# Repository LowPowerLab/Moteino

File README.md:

Moteino
=======

Moteino Eagle project and library.
Moteino is now shipping with DualOptiboot: https://github.com/LowPowerLab/DualOptiboot
DualOptiboot allows for wireless programming using an external FLASH chip soldered to Moteino on the provided footprint.

#License
CC-BY-SA 4.0
https://creativecommons.org/licenses/by-sa/4.0/
You are free to share and adapt. But you need to give attribution and use the same license to redistribute.

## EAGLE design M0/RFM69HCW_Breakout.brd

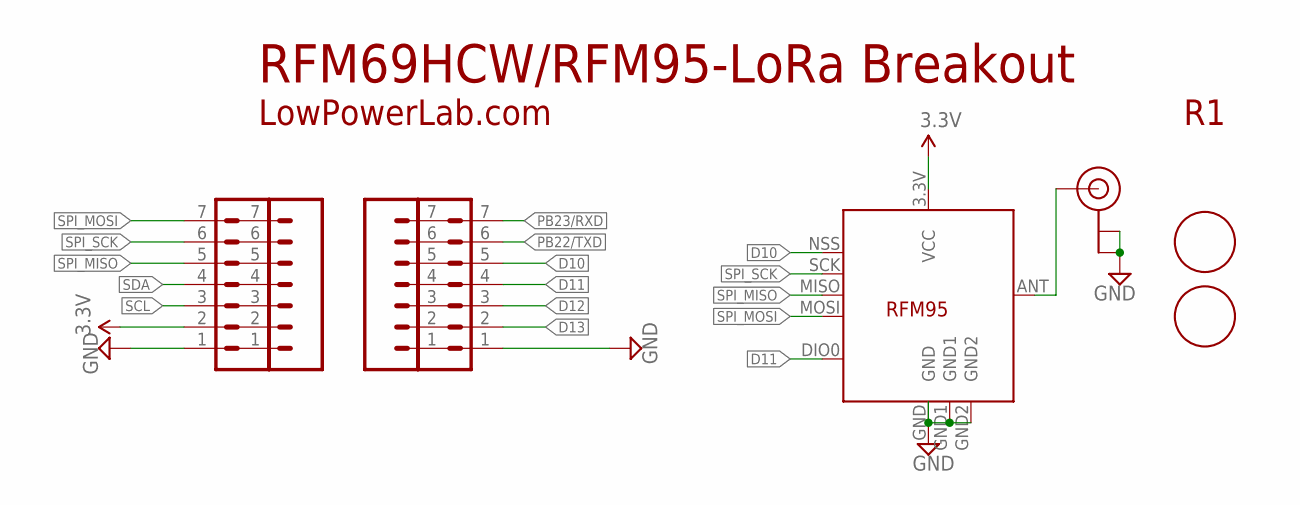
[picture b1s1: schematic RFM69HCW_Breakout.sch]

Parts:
FIDUCIAL_UPPERLEFT: FIDUCIAL1.5MM; FIDUCIAL_1.5MM
U$4, U$10: HDR_7PINNS_THINRINGS; 1X07_NS_THINRINGS
U$9: FIDUCIAL1.5MM; FIDUCIAL_1.5MM
U$16: RFM95COMPACT; RFM95
U$17, U$18: HDR_7PINHH; 1X07_NS_THINRINGS_HH
X2: U.FLW; U.FL_WIDER

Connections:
3.3V: U$16.3.3V (VCC), U$18.2
ANT: U$16.ANT, X2.SIGNAL
D10: U$16.NSS (SEL), U$17.5
D11: U$16.DIO0, U$17.4
D12: U$17.3
D13: U$17.2
GND: U$16.GND, U$16.GND1, U$16.GND2, U$17.1, U$18.1, X2.GND1 (GND), X2.GND2 (GND)
PB22/TXD: U$17.6
PB23/RXD: U$17.7
SCL: U$18.3
SDA: U$18.4
SPI_MISO: U$16.MISO, U$18.5
SPI_MOSI: U$16.MOSI, U$18.7
SPI_SCK: U$16.SCK, U$18.6

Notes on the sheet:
LowPowerLab.com
RFM69HCW/RFM95-LoRa Breakout

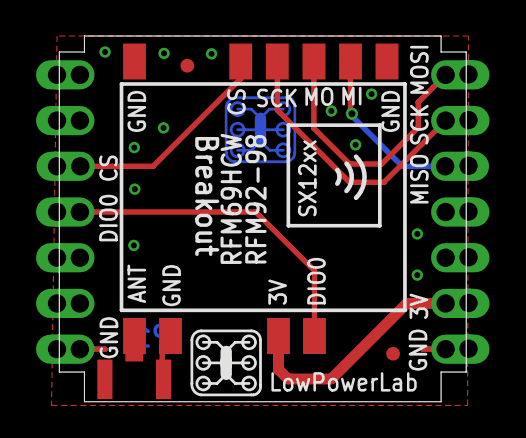
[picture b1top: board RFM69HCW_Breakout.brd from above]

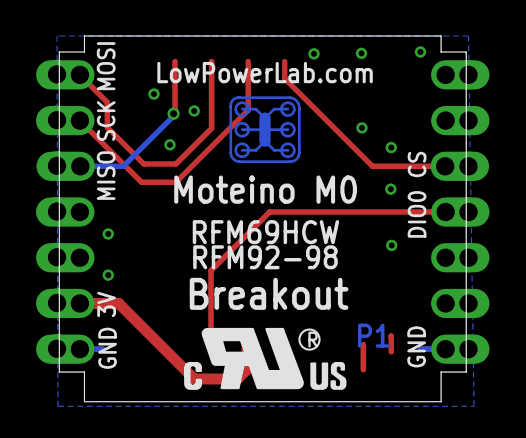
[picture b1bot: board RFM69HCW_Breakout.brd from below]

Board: 2 copper layers, 22.6 x 20.3 mm, 12 parts (4 on the bottom side), 8 nets.

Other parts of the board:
U$1: LOGO_LOWPOWERLAB
U$2: LOGO_UL
U$3: LOGO_LOWPOWERLAB_COPPER
U$7: LOGO_LOWPOWERLAB_STOP

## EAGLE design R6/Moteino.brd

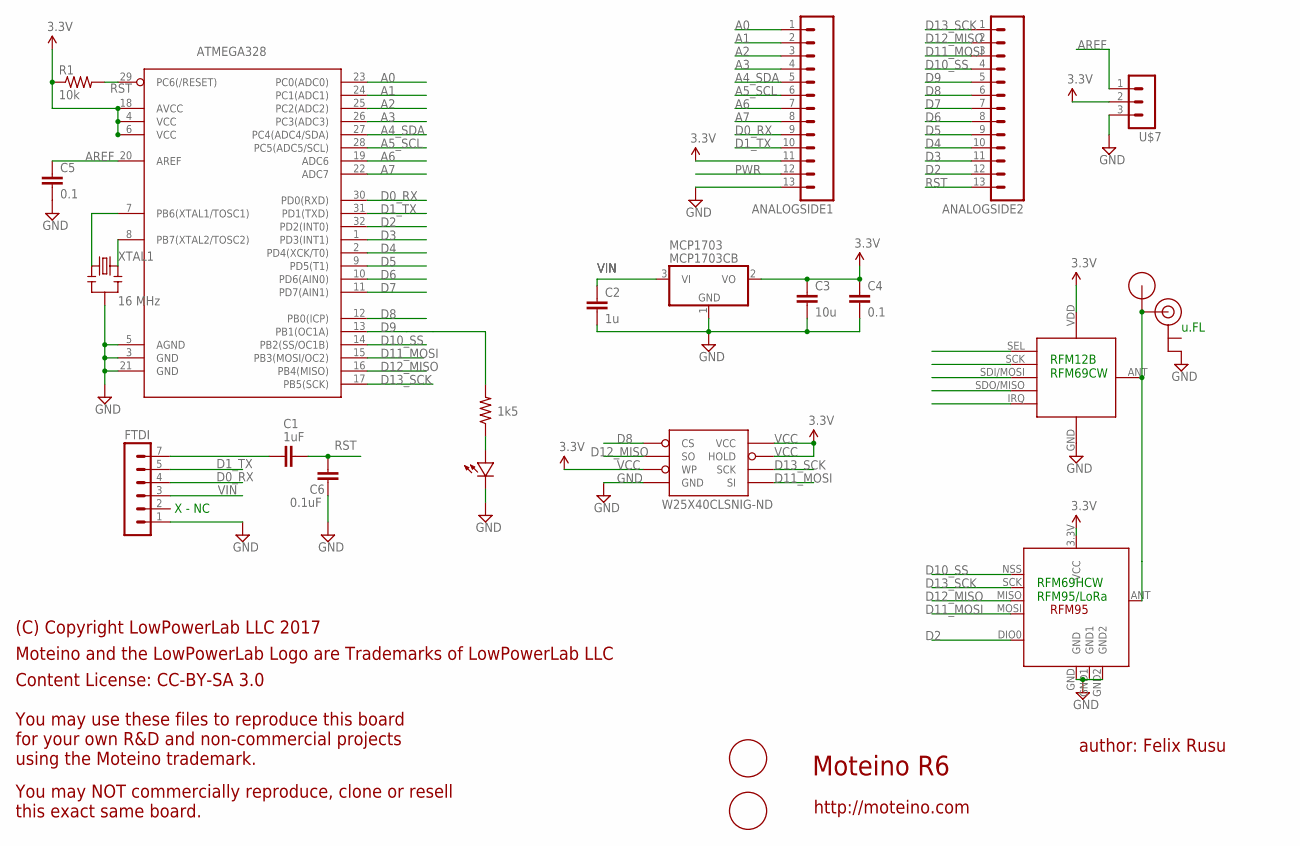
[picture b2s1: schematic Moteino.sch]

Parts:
ANALOGSIDE1, ANALOGSIDE2: HDR_13PINTHIN_RINGS; 1X13_THINRINGS
ATMEGA328: ATMega-328; TQFP32-08
C1: 1uF; 0603-CAP
C2: 1u; 0603-CAP
C3: 10u; 0805-CAP
C4, C5: 0.1; 0603-CAP
C6: 0.1uF; 0603-CAP
FTDI: HDR_6PINTHINRINGS; 1X06_NS_THINRINGS
LED: LED0603; 0603-LED
MCP1703: MCP1703CB; SOT23
R1: 10k; 0603-RES
R2: 1k5; 0603-RES
U$1: RFM12B_ANTENNA""; RFM12B-ANTENNA
U$2: RFM95LONGER; RFM95_LONGER
U$4: U.FL
U$5, U$6: FIDUCIAL1.5MM; FIDUCIAL_1.5MM
U$7: HDR_3PINTHINRINGS; 1X03_NS_THINRINGS
U$8: RFM12B_MINPADS; RFM12B-MINPADS
W25X40CLSNIG-ND: AT25F512BJEDEC_3.9MM; SO08
XTAL1: 16 MHz; RESONATOR-SMD

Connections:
A0: ANALOGSIDE1.1, ATMEGA328.23 (PC0(ADC0))
A1: ANALOGSIDE1.2, ATMEGA328.24 (PC1(ADC1))
A2: ANALOGSIDE1.3, ATMEGA328.25 (PC2(ADC2))
A3: ANALOGSIDE1.4, ATMEGA328.26 (PC3(ADC3))
A4_SDA: ANALOGSIDE1.5, ATMEGA328.27 (PC4(ADC4/SDA))
A5_SCL: ANALOGSIDE1.6, ATMEGA328.28 (PC5(ADC5/SCL))
A6: ANALOGSIDE1.7, ATMEGA328.19 (ADC6)
A7: ANALOGSIDE1.8, ATMEGA328.22 (ADC7)
AREF: ATMEGA328.20 (AREF), C5.1, U$7.1
D0_RX: ANALOGSIDE1.9, ATMEGA328.30 (PD0(RXD)), FTDI.4
D1_TX: ANALOGSIDE1.10, ATMEGA328.31 (PD1(TXD)), FTDI.5
D2: ANALOGSIDE2.12, ATMEGA328.32 (PD2(INT0)), U$2.DIO0, U$8.IRQ
D3: ANALOGSIDE2.11, ATMEGA328.1 (PD3(INT1))
D4: ANALOGSIDE2.10, ATMEGA328.2 (PD4(XCK/T0))
D5: ANALOGSIDE2.9, ATMEGA328.9 (PD5(T1))
D6: ANALOGSIDE2.8, ATMEGA328.10 (PD6(AIN0))
D7: ANALOGSIDE2.7, ATMEGA328.11 (PD7(AIN1))
D8: ANALOGSIDE2.6, ATMEGA328.12 (PB0(ICP)), W25X40CLSNIG-ND.1_CS (CS)
D9: ANALOGSIDE2.5, ATMEGA328.13 (PB1(OC1A)), R2.2
D10_SS: ANALOGSIDE2.4, ATMEGA328.14 (PB2(SS/OC1B)), U$2.NSS (SEL), U$8.SEL
D11_MOSI: ANALOGSIDE2.3, ATMEGA328.15 (PB3(MOSI/OC2)), U$2.MOSI, U$8.SDI/MOSI, W25X40CLSNIG-ND.5_SI (SI)
D12_MISO: ANALOGSIDE2.2, ATMEGA328.16 (PB4(MISO)), U$2.MISO, U$8.SDO/MISO, W25X40CLSNIG-ND.2_SO (SO)
D13_SCK: ANALOGSIDE2.1, ATMEGA328.17 (PB5(SCK)), U$2.SCK, U$8.SCK, W25X40CLSNIG-ND.6_SCK (SCK)
GND: ANALOGSIDE1.13, ATMEGA328.3 (GND), ATMEGA328.5 (AGND), ATMEGA328.21 (GND), C2.2, C3.2, C4.2, C5.2, C6.2, FTDI.1, LED.MINUS, MCP1703.1 (GND), U$2.GND, U$2.GND1, U$2.GND2, U$4.GND2 (GND), U$7.3, U$8.GND, W25X40CLSNIG-ND.4_GND (GND), XTAL1.2
unnamed: ATMEGA328.7 (PB6(XTAL1/TOSC1)), XTAL1.1
unnamed: LED.PLUS, R2.1
unnamed: U$1.P$1, U$2.ANT, U$4.SIGNAL, U$8.ANT
unnamed: C1.2, FTDI.7 (6)
unnamed: ATMEGA328.8 (PB7(XTAL2/TOSC2)), XTAL1.3
PWR: ANALOGSIDE1.12
RST: ANALOGSIDE2.13, ATMEGA328.29 (PC6(/RESET)), C1.1, C6.1, R1.2
VCC: ANALOGSIDE1.11, ATMEGA328.4 (VCC), ATMEGA328.6 (VCC), ATMEGA328.18 (AVCC), C3.1, C4.1, MCP1703.2 (VO), R1.1, U$2.3.3V (VCC), U$7.2, U$8.VDD, W25X40CLSNIG-ND.3_WP (WP), W25X40CLSNIG-ND.7_HOLD (HOLD), W25X40CLSNIG-ND.8_VCC (VCC)
VIN: C2.1, FTDI.3, MCP1703.3 (VI)

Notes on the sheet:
Moteino R6
author: Felix Rusu
http://moteino.com
RFM69HCW RFM95/LoRa
RFM12B RFM69CW
X - NC
u.FL
(C) Copyright LowPowerLab LLC 2017
Moteino and the LowPowerLab Logo are Trademarks of LowPowerLab LLC
Content License: CC-BY-SA 3.0
You may use these files to reproduce this board for your own R&D and non-commercial projects using the Moteino trademark.
You may NOT commercially reproduce, clone or resell this exact same board.

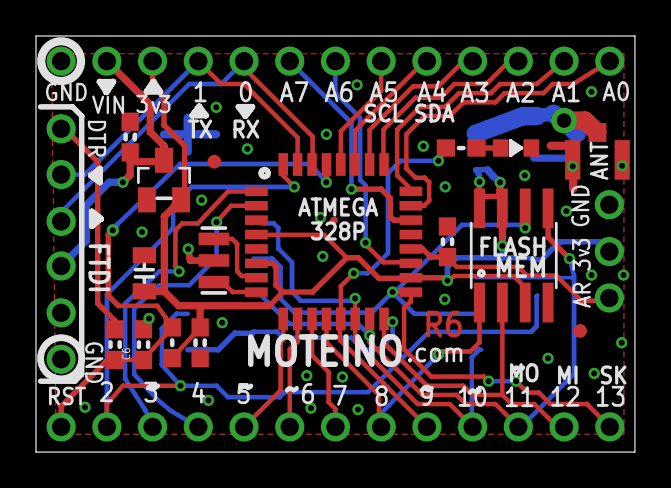
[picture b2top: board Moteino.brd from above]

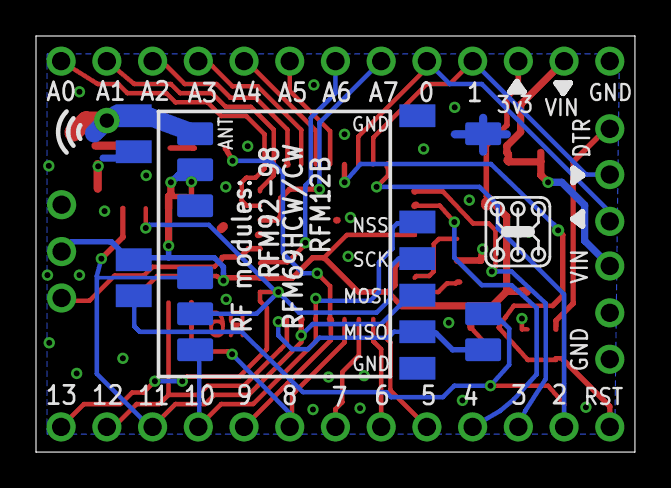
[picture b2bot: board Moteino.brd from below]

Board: 2 copper layers, 33.3 x 23.1 mm, 24 parts (3 on the bottom side), 32 nets.

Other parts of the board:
U$3: LOGO_LOWPOWERLAB

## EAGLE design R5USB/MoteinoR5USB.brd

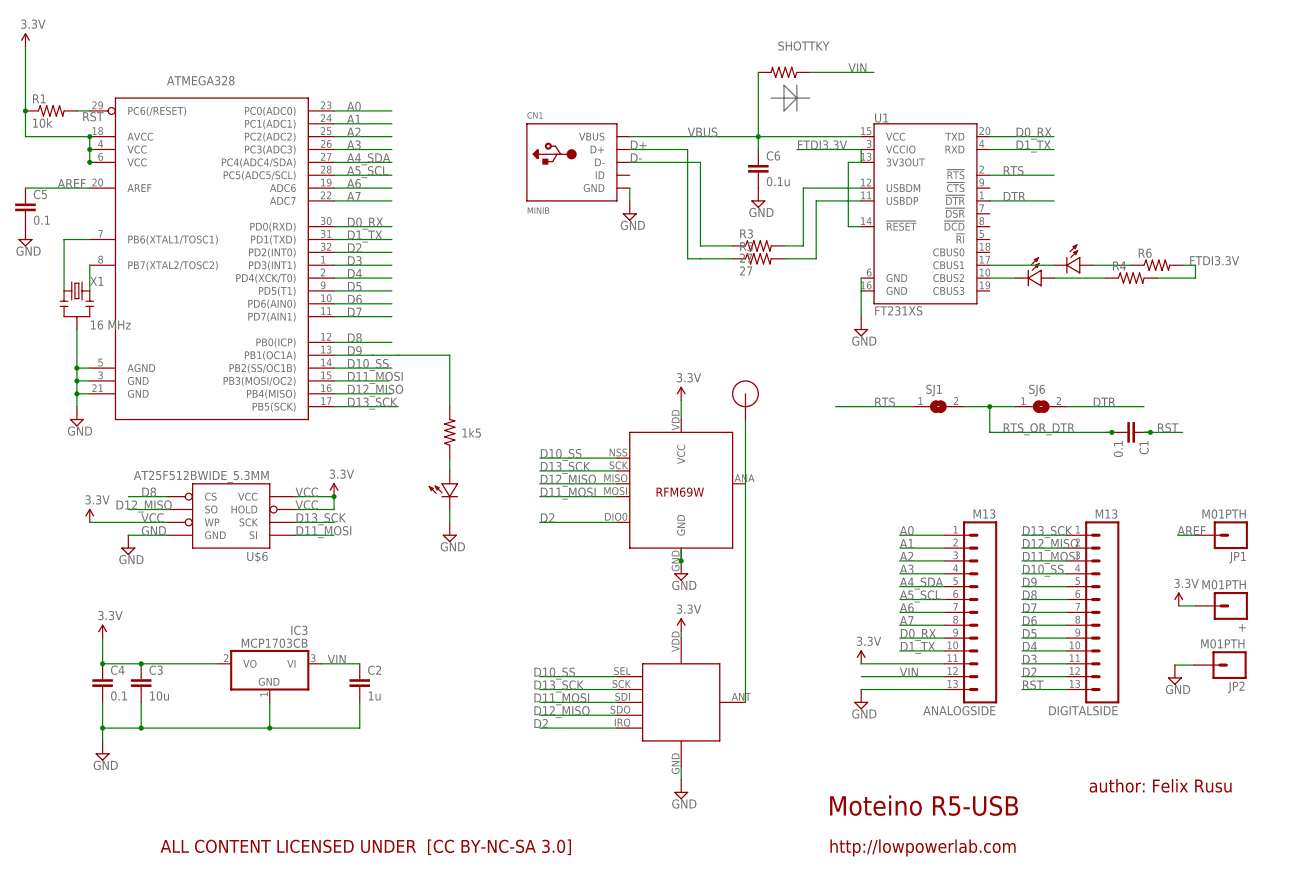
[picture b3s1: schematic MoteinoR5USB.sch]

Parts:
+: M01PTH; 1X01
ANALOGSIDE: M13; 1X13
ATMEGA328: ATMega-328; TQFP32-08
C1, C4, C5: 0.1; 0603-CAP
C2: 1u; 0603-CAP
C3: 10u; 0805-CAP
C6: 0.1u; 0603-CAP
CN1: MINIB; USB-MINIB
D: SHOTTKY; 0603-RES
DIGITALSIDE: M13; 1X13
IC3: MCP1703CB; SOT23
JP1, JP2: M01PTH; 1X01
R1: 10k; 0603-RES
R2: 1k5; 0603-RES
R3, R5: 27; 0603-RES
R4, R6: RESISTOR0603-RES; 0603-RES
RFM12B: RFM12B_MINPADS; RFM12B-MINPADS
SJ1, SJ6: JUMPER; SJW
U1: FT231XS; SSOP20_L
U$1: RFM12B_ANTENNA; RFM12B-ANTENNA
U$2, U$4, U$7: LED0603; 0603-LED
U$5: RFM69; RFM69W-MINPADS
U$6: AT25F512BWIDE_5.3MM; SO08WIDE
X1: 16 MHz; RESONATOR-SMD

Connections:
A0: ANALOGSIDE.1, ATMEGA328.23 (PC0(ADC0))
A1: ANALOGSIDE.2, ATMEGA328.24 (PC1(ADC1))
A2: ANALOGSIDE.3, ATMEGA328.25 (PC2(ADC2))
A3: ANALOGSIDE.4, ATMEGA328.26 (PC3(ADC3))
A4_SDA: ANALOGSIDE.5, ATMEGA328.27 (PC4(ADC4/SDA))
A5_SCL: ANALOGSIDE.6, ATMEGA328.28 (PC5(ADC5/SCL))
A6: ANALOGSIDE.7, ATMEGA328.19 (ADC6)
A7: ANALOGSIDE.8, ATMEGA328.22 (ADC7)
AREF: ATMEGA328.20 (AREF), C5.1, JP1.1
D0_RX: ANALOGSIDE.9, ATMEGA328.30 (PD0(RXD)), U1.20 (TXD)
D1_TX: ANALOGSIDE.10, ATMEGA328.31 (PD1(TXD)), U1.4 (RXD)
D2: ATMEGA328.32 (PD2(INT0)), DIGITALSIDE.12, RFM12B.IRQ, U$5.DIO0
D3: ATMEGA328.1 (PD3(INT1)), DIGITALSIDE.11
D4: ATMEGA328.2 (PD4(XCK/T0)), DIGITALSIDE.10
D5: ATMEGA328.9 (PD5(T1)), DIGITALSIDE.9
D6: ATMEGA328.10 (PD6(AIN0)), DIGITALSIDE.8
D7: ATMEGA328.11 (PD7(AIN1)), DIGITALSIDE.7
D8: ATMEGA328.12 (PB0(ICP)), DIGITALSIDE.6, U$6.1 (CS)
D9: ATMEGA328.13 (PB1(OC1A)), DIGITALSIDE.5, R2.2
D10_SS: ATMEGA328.14 (PB2(SS/OC1B)), DIGITALSIDE.4, RFM12B.SEL, U$5.NSS (SEL)
D11_MOSI: ATMEGA328.15 (PB3(MOSI/OC2)), DIGITALSIDE.3, RFM12B.SDI (SDI/MOSI), U$5.MOSI, U$6.5 (SI)
D12_MISO: ATMEGA328.16 (PB4(MISO)), DIGITALSIDE.2, RFM12B.SDO (SDO/MISO), U$5.MISO, U$6.2 (SO)
D13_SCK: ATMEGA328.17 (PB5(SCK)), DIGITALSIDE.1, RFM12B.SCK, U$5.SCK, U$6.6 (SCK)
D+: CN1.D+, R5.1
D-: CN1.D-, R3.1
DTR: SJ6.2, U1.1 (!DTR)
FTDI3.3V: R4.2, R6.2, U1.3 (VCCIO), U1.13 (3V3OUT), U1.14 (!RESET)
GND: ANALOGSIDE.13, ATMEGA328.3 (GND), ATMEGA328.5 (AGND), ATMEGA328.21 (GND), C2.2, C3.2, C4.2, C5.2, C6.2, CN1.GND, IC3.1 (GND), JP2.1, RFM12B.GND, U1.6 (GND), U1.16 (GND), U$2.MINUS, U$5.GND, U$6.4 (GND), X1.2
unnamed: ATMEGA328.7 (PB6(XTAL1/TOSC1)), X1.1
unnamed: R2.1, U$2.PLUS
unnamed: RFM12B.ANT, U$1.P$1, U$5.ANA (ANT)
unnamed: R3.2, U1.12 (USBDM)
unnamed: R5.2, U1.11 (USBDP)
unnamed: U1.17 (CBUS1), U$4.MINUS
unnamed: U1.10 (CBUS2), U$7.MINUS
unnamed: R4.1, U$7.PLUS
unnamed: R6.1, U$4.PLUS
unnamed: ATMEGA328.8 (PB7(XTAL2/TOSC2)), X1.3
RST: ATMEGA328.29 (PC6(/RESET)), C1.1, DIGITALSIDE.13, R1.2
RTS: SJ1.1, U1.2 (!RTS)
RTS_OR_DTR: C1.2, SJ1.2, SJ6.1
VBUS: C6.1, CN1.VBUS, D.2, U1.15 (VCC)
VCC: +.1, ANALOGSIDE.11, ATMEGA328.4 (VCC), ATMEGA328.6 (VCC), ATMEGA328.18 (AVCC), C3.1, C4.1, IC3.2 (VO), R1.1, RFM12B.VDD, U$5.VDD (VCC), U$6.3 (WP), U$6.7 (HOLD), U$6.8 (VCC)
VIN: ANALOGSIDE.12, C2.1, D.1, IC3.3 (VI)

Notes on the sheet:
Moteino R5-USB
author: Felix Rusu
http://lowpowerlab.com
ALL CONTENT LICENSED UNDER [CC BY-NC-SA 3.0]

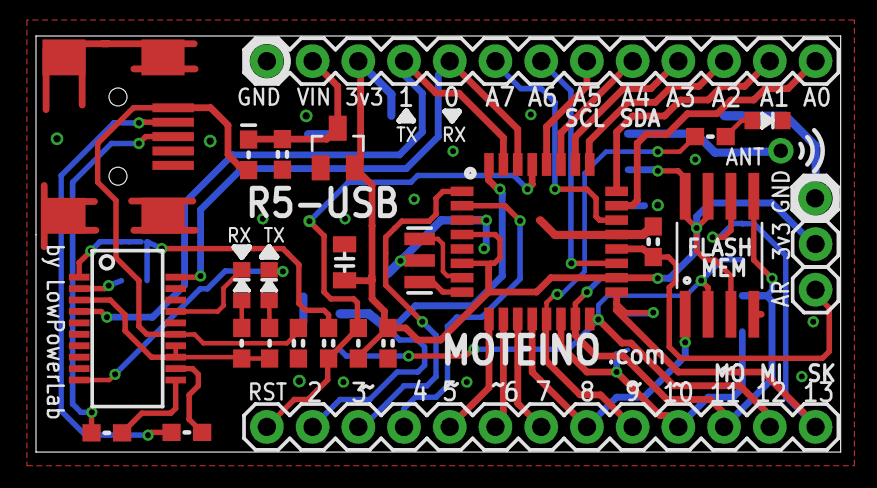
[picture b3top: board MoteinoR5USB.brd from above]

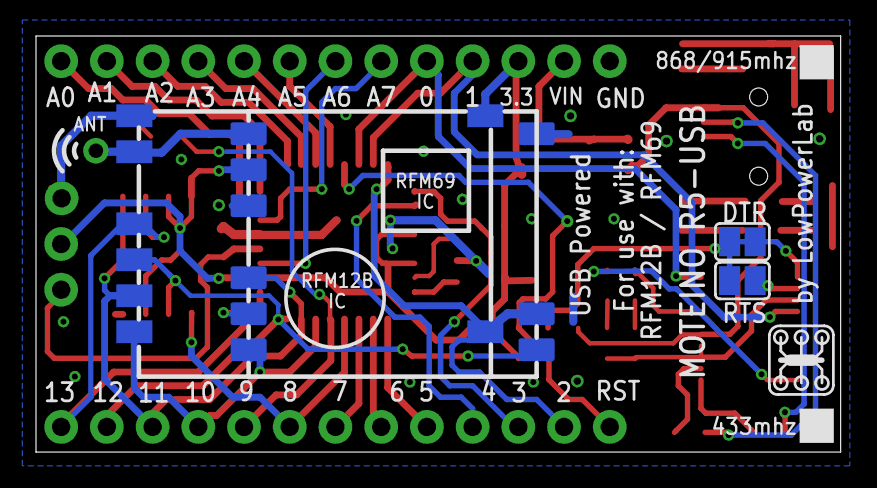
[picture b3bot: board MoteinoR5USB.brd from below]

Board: 2 copper layers, 44.7 x 23.1 mm, 33 parts (5 on the bottom side), 44 nets.

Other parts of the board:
U$3: LOGO_LOWPOWERLAB

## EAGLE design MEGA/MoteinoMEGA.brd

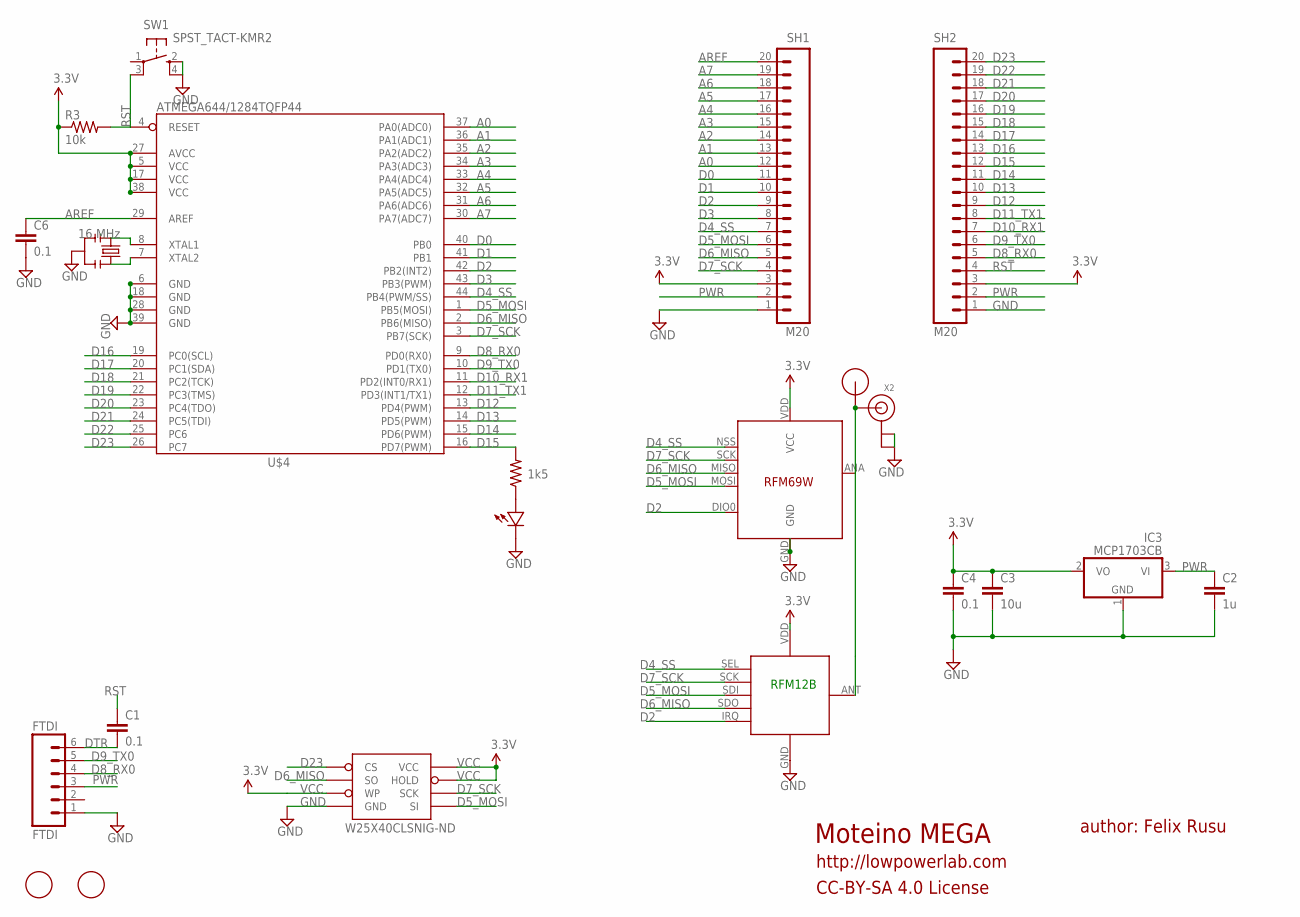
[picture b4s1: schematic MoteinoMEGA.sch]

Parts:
C1, C4, C6: 0.1; 0603-CAP
C2: 1u; 0603-CAP
C3: 10u; 0805-CAP
FTDI: FTDI; 1X06
IC3: MCP1703CB; SOT23
R2: 1k5; 0603-RES
R3: 10k; 0603-RES
RFM12B: RFM12B_MINPADS; RFM12B-MINPADS
SH1, SH2: M20; 1X20
SW1: SPST_TACT-KMR2; KMR2
U$1: RFM12B_ANTENNA; RFM12B-ANTENNA
U$2, U$7: FIDUCIAL; FIDUCIAL_1MM
U$4: ATMEGA644/1284TQFP44; TQFP44
U$5: RFM69; RFM69W-MINPADS
U$6: LED0603; 0603-LED
W25X40CLSNIG-ND: AT25F512BWIDE_5.3MM; SO08WIDE
X1: 16 MHz; RESONATOR-SMD
X2: ANTENNA_U.FL; U.FL

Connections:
A0: SH1.12, U$4.37 (PA0(ADC0))
A1: SH1.13, U$4.36 (PA1(ADC1))
A2: SH1.14, U$4.35 (PA2(ADC2))
A3: SH1.15, U$4.34 (PA3(ADC3))
A4: SH1.16, U$4.33 (PA4(ADC4))
A5: SH1.17, U$4.32 (PA5(ADC5))
A6: SH1.18, U$4.31 (PA6(ADC6))
A7: SH1.19, U$4.30 (PA7(ADC7))
AREF: C6.1, SH1.20, U$4.29 (AREF)
D0: SH1.11, U$4.40 (PB0)
D1: SH1.10, U$4.41 (PB1)
D2: RFM12B.IRQ, SH1.9, U$4.42 (PB2(INT2)), U$5.DIO0
D3: SH1.8, U$4.43 (PB3(PWM))
D4_SS: RFM12B.SEL, SH1.7, U$4.44 (PB4(PWM/SS)), U$5.NSS (SEL)
D5_MOSI: RFM12B.SDI (SDI/MOSI), SH1.6, U$4.1 (PB5(MOSI)), U$5.MOSI, W25X40CLSNIG-ND.5 (SI)
D6_MISO: RFM12B.SDO (SDO/MISO), SH1.5, U$4.2 (PB6(MISO)), U$5.MISO, W25X40CLSNIG-ND.2 (SO)
D7_SCK: RFM12B.SCK, SH1.4, U$4.3 (PB7(SCK)), U$5.SCK, W25X40CLSNIG-ND.6 (SCK)
D8_RX0: FTDI.4, SH2.5, U$4.9 (PD0(RX0))
D9_TX0: FTDI.5, SH2.6, U$4.10 (PD1(TX0))
D10_RX1: SH2.7, U$4.11 (PD2(INT0/RX1))
D11_TX1: SH2.8, U$4.12 (PD3(INT1/TX1))
D12: SH2.9, U$4.13 (PD4(PWM))
D13: SH2.10, U$4.14 (PD5(PWM))
D14: SH2.11, U$4.15 (PD6(PWM))
D15: R2.2, SH2.12, U$4.16 (PD7(PWM))
D16: SH2.13, U$4.19 (PC0(SCL))
D17: SH2.14, U$4.20 (PC1(SDA))
D18: SH2.15, U$4.21 (PC2(TCK))
D19: SH2.16, U$4.22 (PC3(TMS))
D20: SH2.17, U$4.23 (PC4(TDO))
D21: SH2.18, U$4.24 (PC5(TDI))
D22: SH2.19, U$4.25 (PC6)
D23: SH2.20, U$4.26 (PC7), W25X40CLSNIG-ND.1 (CS)
DTR: C1.2, FTDI.6
GND: C2.2, C3.2, C4.2, C6.2, FTDI.1, IC3.1 (GND), RFM12B.GND, SH1.1, SH2.1, SW1.2 (S), SW1.4 (S1), U$4.6 (GND), U$4.18 (GND), U$4.28 (GND), U$4.39 (GND), U$5.GND, U$6.MINUS, W25X40CLSNIG-ND.4 (GND), X1.2, X2.1 (GND), X2.2 (GND)
unnamed: U$4.8 (XTAL1), X1.1
unnamed: R2.1, U$6.PLUS
unnamed: RFM12B.ANT, U$1.P$1, U$5.ANA (ANT), X2.3 (SIGNAL)
unnamed: U$4.7 (XTAL2), X1.3
PWR: C2.1, FTDI.3, IC3.3 (VI), SH1.2, SH2.2
RST: C1.1, R3.2, SH2.4, SW1.3 (P1), U$4.4 (RESET)
VCC: C3.1, C4.1, IC3.2 (VO), R3.1, RFM12B.VDD, SH1.3, SH2.3, U$4.5 (VCC), U$4.17 (VCC), U$4.27 (AVCC), U$4.38 (VCC), U$5.VDD (VCC), W25X40CLSNIG-ND.3 (WP), W25X40CLSNIG-ND.7 (HOLD), W25X40CLSNIG-ND.8 (VCC)

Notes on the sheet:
Moteino MEGA
author: Felix Rusu
http://lowpowerlab.com
RFM12B
CC-BY-SA 4.0 License

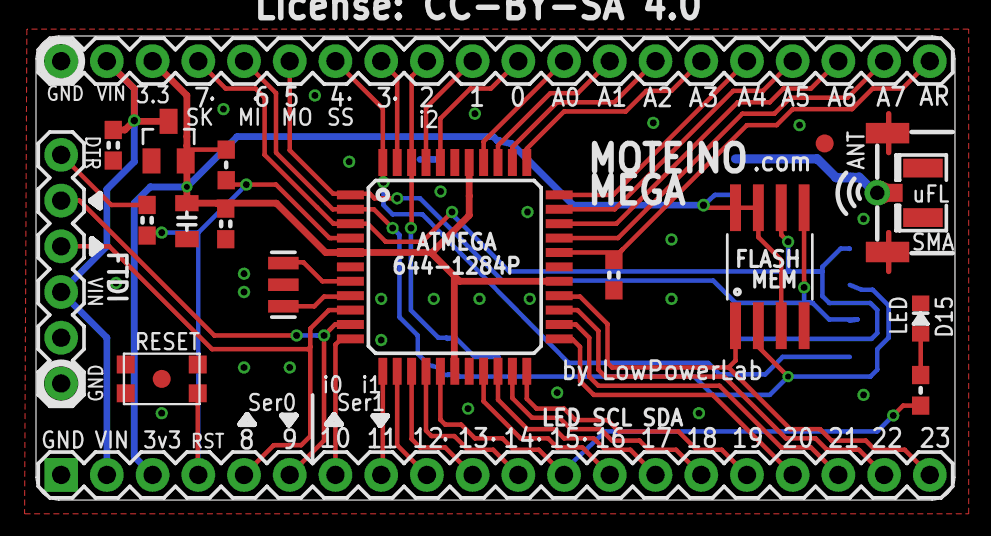
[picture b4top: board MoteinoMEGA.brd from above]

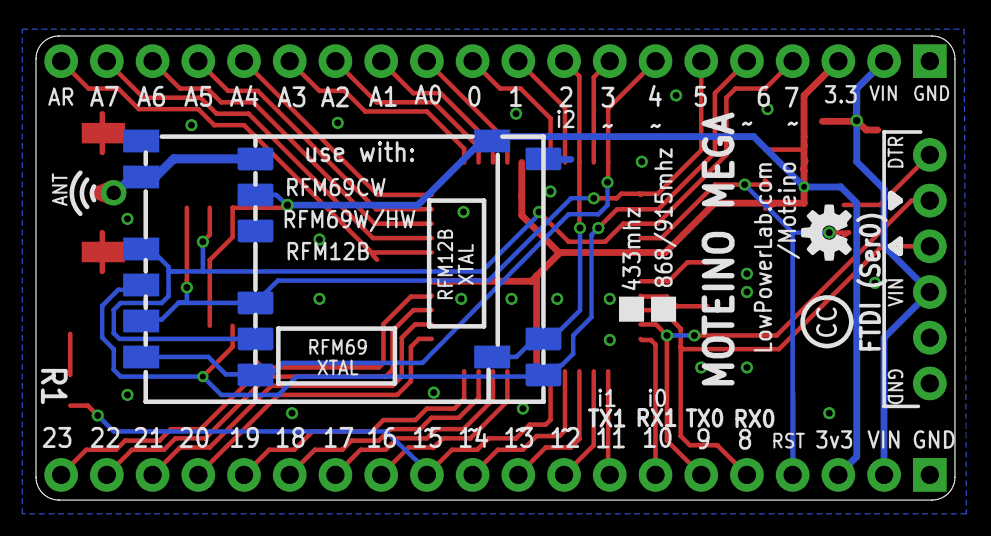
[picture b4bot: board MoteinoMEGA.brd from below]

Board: 2 copper layers, 51.1 x 25.8 mm, 23 parts (3 on the bottom side), 42 nets.

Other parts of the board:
U$3: OSHW-LOGO-S

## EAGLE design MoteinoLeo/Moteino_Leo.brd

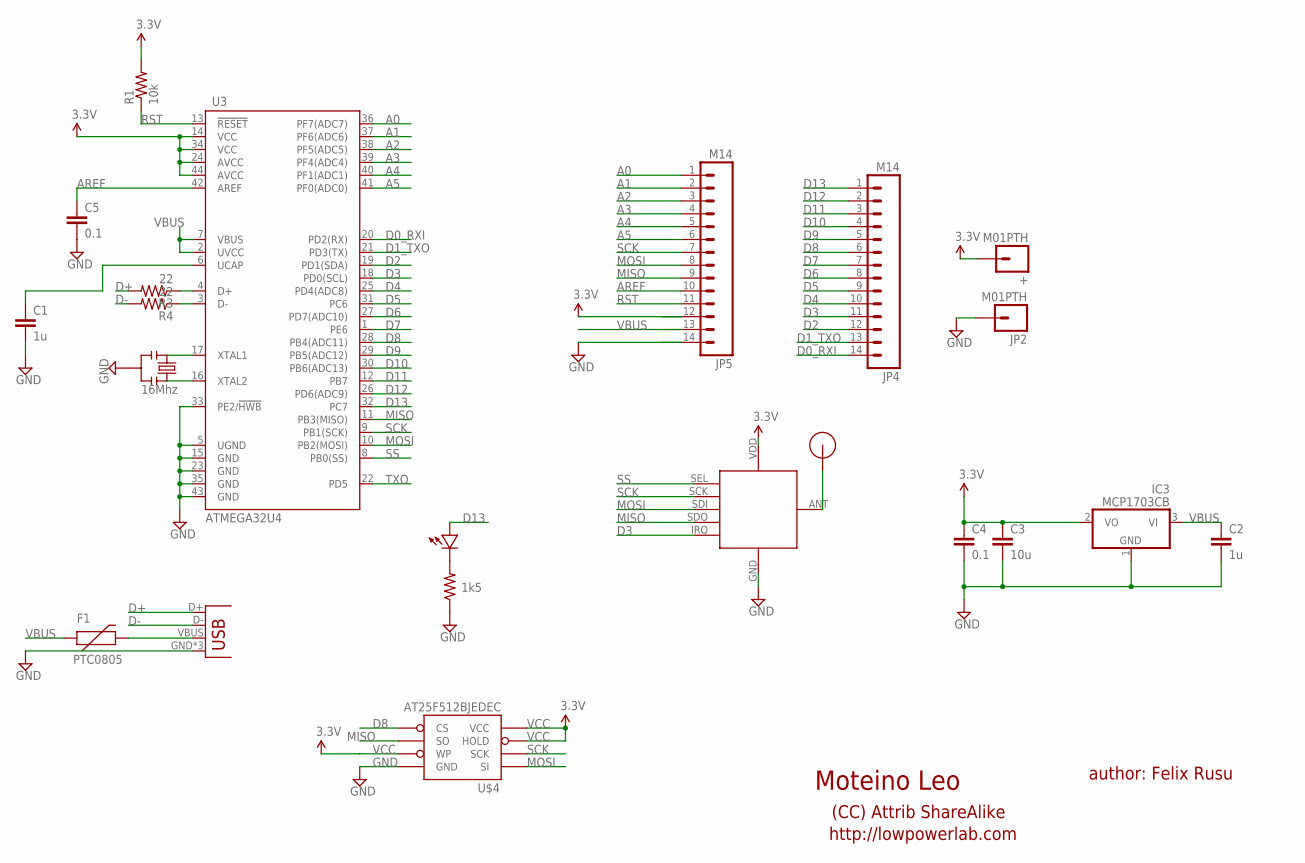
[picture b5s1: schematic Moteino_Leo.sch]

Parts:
+: M01PTH; 1X01
C1, C2: 1u; 0603-CAP
C3: 10u; 0805-CAP
C4, C5: 0.1; 0603-CAP
F1: PTC0805; 0805-PTC
IC3: MCP1703CB; SOT23
JP2: M01PTH; 1X01
JP3: USB-MICROB
JP4, JP5: M14; 1X14
R1: 10k; 0603-RES
R2: 1k5; 0603-RES
R3, R4: 22; 0603-RES
RFM12B: RFM12B_MINPADS; RFM12B-MINPADS
U3: ATMEGA32U4; QFN-44-NOPAD
U$1: RFM12B_ANTENNA; RFM12B-ANTENNA
U$2: LED0603; 0603-LED
U$4: AT25F512BJEDEC; SO08
X1: 16Mhz; RESONATOR-SMD

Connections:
A0: JP5.1, U3.36 (PF7(ADC7))
A1: JP5.2, U3.37 (PF6(ADC6))
A2: JP5.3, U3.38 (PF5(ADC5))
A3: JP5.4, U3.39 (PF4(ADC4))
A4: JP5.5, U3.40 (PF1(ADC1))
A5: JP5.6, U3.41 (PF0(ADC0))
AREF: C5.1, JP5.10, U3.42 (AREF)
D0_RXI: JP4.14, U3.20 (PD2(RX))
D1_TXO: JP4.13, U3.21 (PD3(TX))
D2: JP4.12, U3.19 (PD1(SDA))
D3: JP4.11, RFM12B.IRQ, U3.18 (PD0(SCL))
D4: JP4.10, U3.25 (PD4(ADC8))
D5: JP4.9, U3.31 (PC6)
D6: JP4.8, U3.27 (PD7(ADC10))
D7: JP4.7, U3.1 (PE6)
D8: JP4.6, U3.28 (PB4(ADC11)), U$4.1_CS (CS)
D9: JP4.5, U3.29 (PB5(ADC12))
D10: JP4.4, U3.30 (PB6(ADC13))
D11: JP4.3, U3.12 (PB7)
D12: JP4.2, U3.26 (PD6(ADC9))
D13: JP4.1, U3.32 (PC7), U$2.PLUS
D+: JP3.D+, R3.2
D-: JP3.D-, R4.2
GND: C1.2, C2.2, C3.2, C4.2, C5.2, IC3.1 (GND), JP2.1, JP3.GND, JP3.MT1 (GND), JP3.MT2 (GND), JP5.14, R2.1, RFM12B.GND, U3.5 (UGND), U3.15 (GND), U3.23 (GND), U3.33 (PE2/!HWB), U3.35 (GND), U3.43 (GND), U$4.4_GND (GND), X1.2
MISO: JP5.9, RFM12B.SDO (SDO/MISO), U3.11 (PB3(MISO)), U$4.2_SO (SO)
MOSI: JP5.8, RFM12B.SDI (SDI/MOSI), U3.10 (PB2(MOSI)), U$4.5_SI (SI)
unnamed: R2.2, U$2.MINUS
unnamed: RFM12B.ANT, U$1.P$1
unnamed: U3.16 (XTAL2), X1.3
unnamed: U3.17 (XTAL1), X1.1
unnamed: C1.1, U3.6 (UCAP)
unnamed: R3.1, U3.4 (D+)
unnamed: R4.1, U3.3 (D-)
RST: JP5.11, R1.1, U3.13 (!RESET)
SCK: JP5.7, RFM12B.SCK, U3.9 (PB1(SCK)), U$4.6_SCK (SCK)
SS: RFM12B.SEL, U3.8 (PB0(SS))
TXO: U3.22 (PD5)
USBPOWER: F1.2, JP3.VBUS
VBUS: C2.1, F1.1, IC3.3 (VI), JP5.13, U3.2 (UVCC), U3.7 (VBUS)
VCC: +.1, C3.1, C4.1, IC3.2 (VO), JP5.12, R1.2, RFM12B.VDD, U3.14 (VCC), U3.24 (AVCC), U3.34 (VCC), U3.44 (AVCC), U$4.3_WP (WP), U$4.7_HOLD (HOLD), U$4.8_VCC (VCC)

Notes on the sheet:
Moteino Leo
author: Felix Rusu
http://lowpowerlab.com
(CC) Attrib ShareAlike

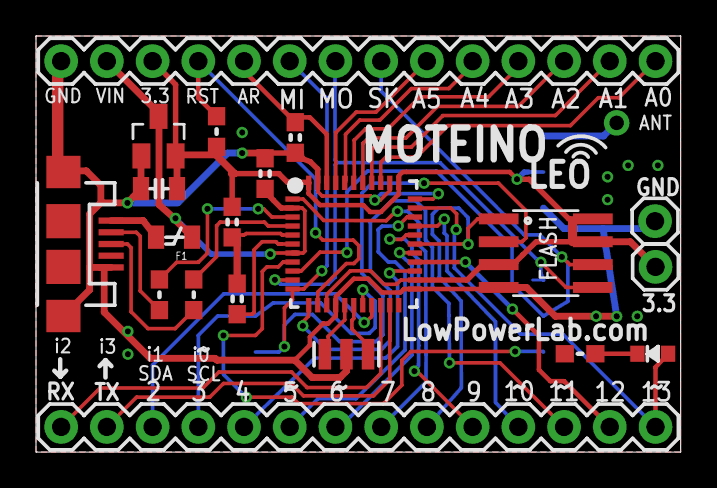
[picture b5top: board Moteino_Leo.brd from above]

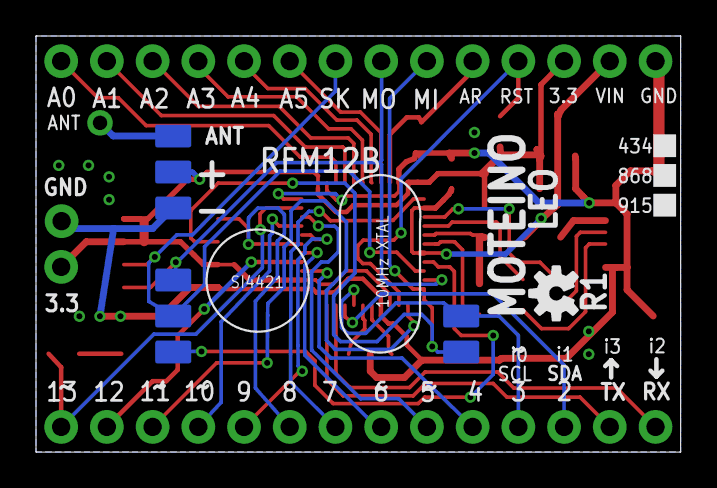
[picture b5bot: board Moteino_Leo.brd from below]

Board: 2 copper layers, 35.8 x 23.1 mm, 23 parts (2 on the bottom side), 39 nets.

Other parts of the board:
U$3: OSHW-LOGO-S

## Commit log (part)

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2012-12-28 Add Moteino Eagle files
2013-03-12 R2 Update
2013-05-30 Update to R1 production schematic
2013-05-30 Update to R1 production board
2013-06-25 Add R2 and R3 Eagle files
2013-10-24 Add Moteino R4 & R4-USB
2013-10-24 Add rendering
2013-10-24 Add renderings
2013-12-23 Update Eagle files, add schematic PDFs
2014-01-21 Remove MFGCode
2014-02-03 Add stencil PNGs
    You can print these on vinyl and then toner transfer to soda can
    interior, then etch it in muriatic acid + hydrogen peroxide (1+3 parts
    solution). Instructions at:
    http://lowpowerlab.com/blog/2013/02/11/diy-smd-metal-stencils-the-definitive-tutorial/
2014-07-29 Update BOM
2014-08-09 Add MoteinoMEGA
2014-08-10 Update Eagle files
2014-08-10 Add MEGA Arduino Core
2014-11-03 Add Moteino DualOptiboot bootloader
2014-11-24 Update MEGA core, include regular Moteino variant
2014-11-28 Typos & license update
2015-04-26 Add dimension files
2015-10-13 Add Motein oR5-USB
2016-02-17 Add LoRa board & schematic
2016-08-04 Basic updates
2016-08-25 Fix pins_arduino.h PCMSK defs
    Fix bug causing SoftwareSerial to not receive on MoteinoMEGA
2017-09-20 Add Moteino library
2017-09-21 small changes
2018-05-06 Add MoteinoR6 design files
2018-11-19 add M0 header layout
2018-11-26 Add MoteinoM0
2019-02-15 Add MoteinoM0_SMD package
2020-09-03 Add RFM69HCW breakout

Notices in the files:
parts and their libraries:
SparkFun-Aesthetics: Licensing: CC v3.0 Share-Alike You are welcome to use this library for commercial purposes.
